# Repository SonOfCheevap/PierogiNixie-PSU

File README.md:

# PierogiNixie-PSU
A simple 12v to 150v-250v DC-DC Power supply for use with nixie tubes.

This is a modified version of an already existing PSU. Link to the original: https://www.electronics-lab.com/project/hv-nixie-dc-dc-switching-power-supply/

## New with V1.2
- Adjustable output AND hardwired resistor options available (150V-250V with variable resistor, 170V with set resistor)
- Cleaner routing
- Power planes
- Updated schematic to be more readable
- Included schematic as PDF
- Smaller Footprint

# Features
- 12v barrel jack input and wire input
- Adjustable output range of 150V to 250V (Only on V1 and V1.2)
- Wire output
- Mounting for M3.5x6 Screw

# Pictures
V1.2 AS OF 1/3/2025

### Front

### Back

### Render

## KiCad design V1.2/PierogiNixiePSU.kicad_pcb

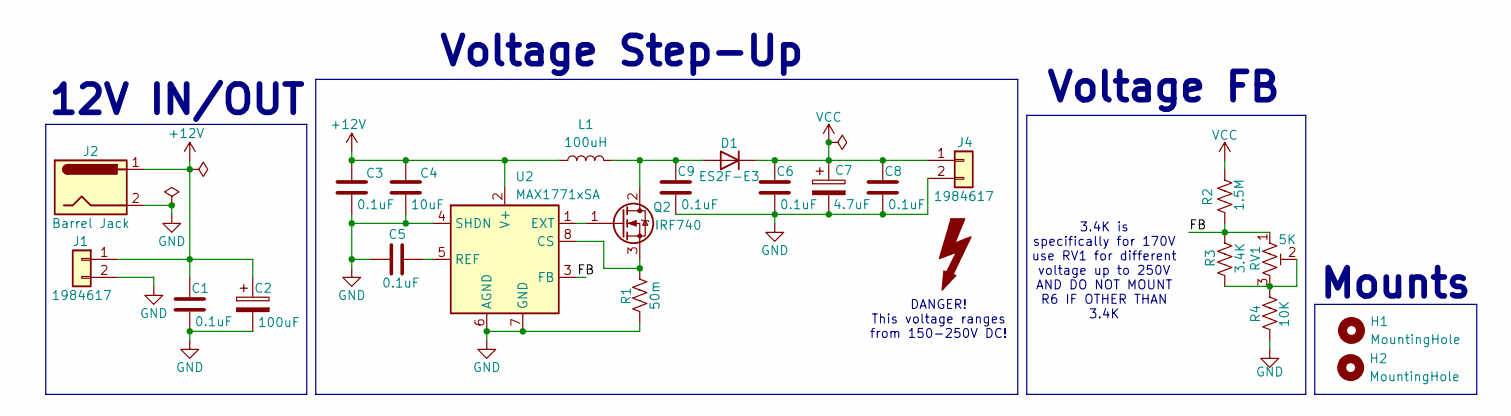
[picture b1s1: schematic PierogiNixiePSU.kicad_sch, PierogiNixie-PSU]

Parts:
C1, C3, C5, C6, C8, C9: 0.1uF; C_0805_2012Metric
C2: 100uF; CP_EIA-7343-30_AVX-N; Manufacturer_Part_Number TAJD107K020RNJ; Mouser Part Number 581-TAJD107K020R
C4: 10uF; C_0805_2012Metric
C7: 4.7uF; CP_Radial_D6.3mm_P2.50mm
D1: ES2F-E3; D_SMB_Handsoldering
H1, H2: MountingHole; MountingHole_3.5mm
J1, J4: 1984617; PhoenixContact_MCV_1,5_2-G-3.5_1x02_P3.50mm_Vertical
J2: Barrel Jack; BarrelJack_Kycon_KLDX-0202-xC_Horizontal
L1: 100uH; L_Vishay_IHLP-4040
Q2: IRF740; TO-263-2
R1: 50m; R_0805_2012Metric
R2: 1.5M; R_0805_2012Metric
R3: 3.4K; R_0805_2012Metric
R4: 10K; R_0805_2012Metric
RV1: 5K; Potentiometer_Bourns_3386P_Vertical
U2: MAX1771xSA; SO-8_3.9x4.9mm_P1.27mm

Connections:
+12V: C1.1, C2.1, C3.1, C4.1, J1.1, J2.1, L1.1, U2.2 (V+)
/FB: R2.1, R3.2, RV1.1, U2.3 (FB)
GND: C1.2, C2.2, C3.2, C4.2, C5.2, C6.2, C7.2, C8.2, C9.2, J1.2, J2.2, J4.2, R1.1, R4.2, U2.4 (SHDN), U2.6 (AGND), U2.7 (GND)
unnamed: C9.1, D1.2 (A), L1.2, Q2.2 (D)
unnamed: Q2.1 (G), U2.1 (EXT)
unnamed: Q2.3 (S), R1.2, U2.8 (CS)
unnamed: R3.1, R4.1, RV1.2, RV1.3
unnamed: C5.1, U2.5 (REF)
VCC: C6.1, C7.1, C8.1, D1.1 (K), J4.1, R2.2

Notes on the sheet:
Mounts
12V IN/OUT
Voltage FB
3.4K is specifically for 170V use RV1 for different voltage up to 250V AND DO NOT MOUNT R6 IF OTHER THAN 3.4K
Voltage Step-Up
DANGER! This voltage ranges from 150-250V DC!

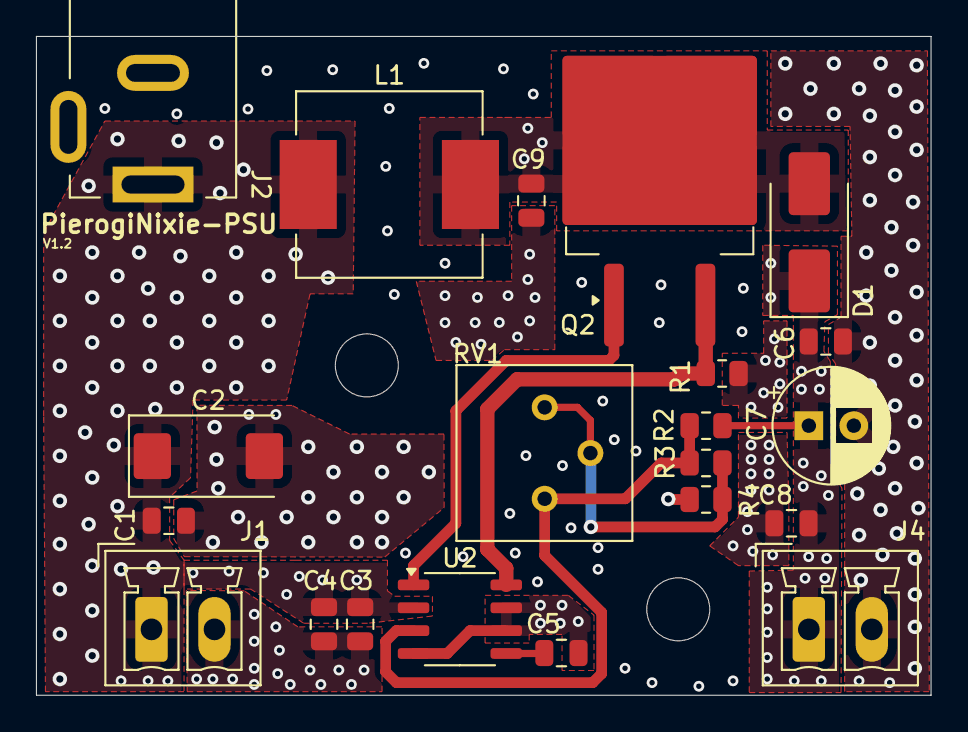
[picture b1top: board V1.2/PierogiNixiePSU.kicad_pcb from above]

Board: 4 copper layers, 49.7 x 36.6 mm, 23 parts (0 on the bottom side), 9 nets.

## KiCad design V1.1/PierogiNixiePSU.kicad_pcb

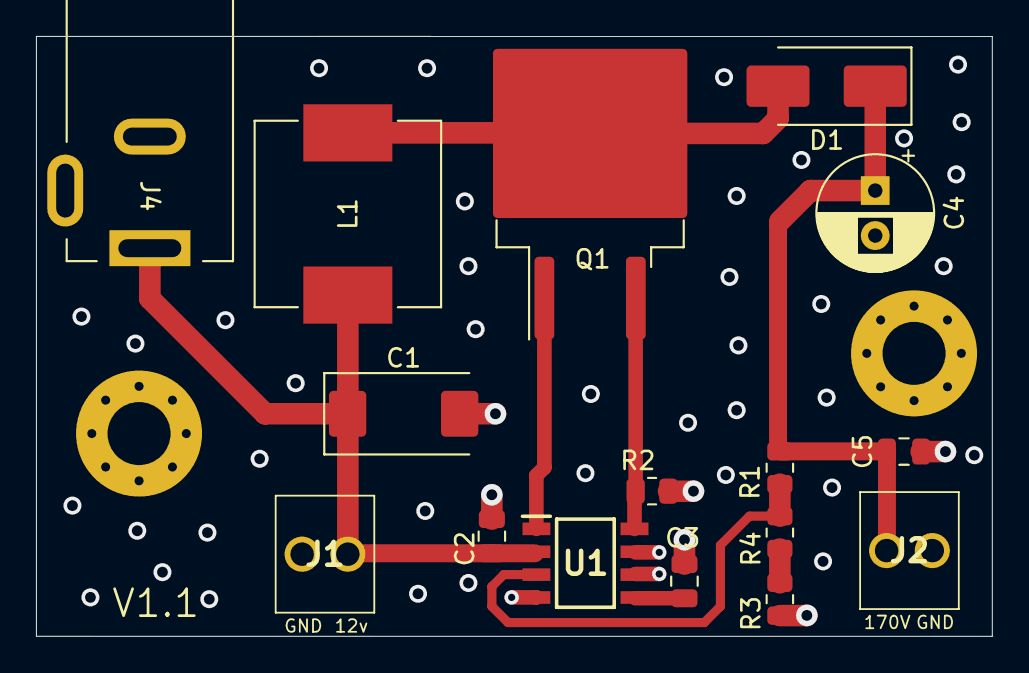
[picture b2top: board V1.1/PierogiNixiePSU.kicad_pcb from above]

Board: 4 copper layers, 53.1 x 33.3 mm, 18 parts (0 on the bottom side), 9 nets.

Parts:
C1: 100uF; CP_EIA-7343-30_AVX-N
C2, C3: 100nF; C_0805_2012Metric
C4: 4.7uF; CP_Radial_D6.3mm_P2.50mm
C5: .1uF; C_0805_2012Metric
D1: ES2F-E3; D_SMB_Handsoldering
H1, H2: MountingHole; MountingHole_3.5mm_Pad_Via
J1, J2: OSTVN02A150
J4: Barrel_Jack; BarrelJack_Kycon_KLDX-0202-xC_Horizontal
L1: 100uH; L_Vishay_IHLP-4040
Q1: IRF740STRLPBF; TO-263-2
R1: 1.5M; R_0805_2012Metric
R2: 50m; R_0805_2012Metric
R3: 10k; R_0805_2012Metric
R4: 3.4K; R_0805_2012Metric
U1: MAX1771CSAT; SOIC127P600X175-8N

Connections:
/CS: Q1.3 (S), R2.2, U1.8 (CS)
/EXT: Q1.1 (G), U1.1 (EXT)
/FB: R1.1, R4.2, U1.3 (FB)
GND: C1.2, C2.2, C3.2, C4.2, C5.2, J1.1, J2.2, J4.2, R2.1, R3.2, U1.4 (SHDN), U1.6 (AGND), U1.7 (GND)
unnamed: D1.2 (A), L1.2, Q1.2 (D)
unnamed: C4.1, C5.1, D1.1 (K), J2.1, R1.2
unnamed: R3.1, R4.1
unnamed: C3.1, U1.5 (REF)
unnamed: C1.1, C2.1, J1.2, J4.1, L1.1, U1.2 (V+)

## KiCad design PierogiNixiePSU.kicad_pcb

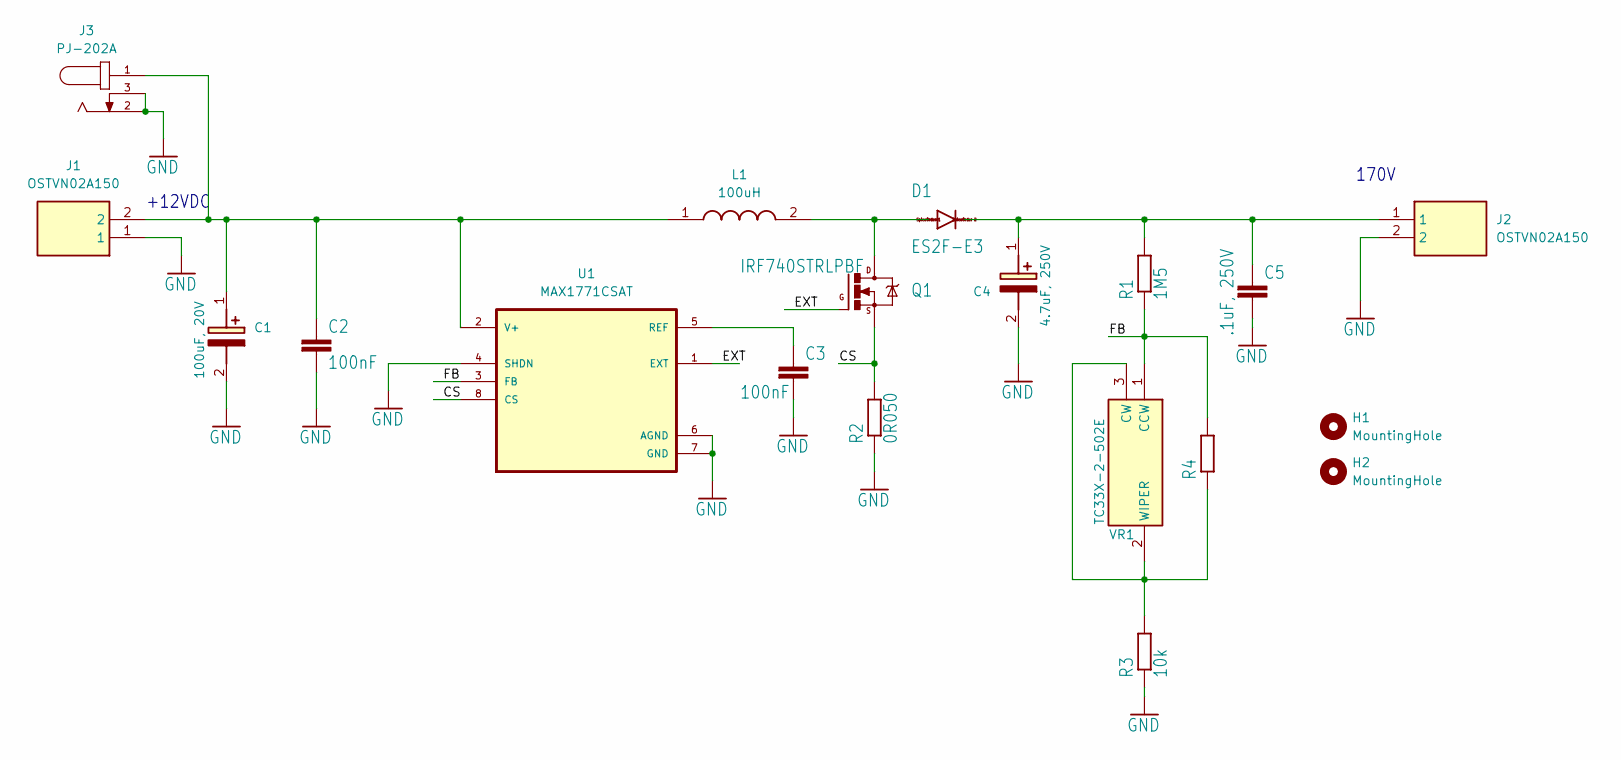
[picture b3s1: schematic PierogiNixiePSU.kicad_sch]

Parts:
C1: 100uF, 20V; CAPPM7344X310N; Manufacturer_Part_Number TAJD107K020RNJ; Mouser Part Number 581-TAJD107K020R
C2, C3: 100nF; C0805
C4: 4.7uF, 250V; CAPPRD250W50D655H1250; Manufacturer_Part_Number UVK2D0R1MED1TD
C5: .1uF, 250V; C0805
D1: ES2F-E3; SMB
H1, H2: MountingHole; MountingHole_3.5mm_Pad_Via
J1, J2: OSTVN02A150; Manufacturer_Part_Number OSTVN02A150
J3: PJ-202A; CUI_PJ-202A; PART_REV 1.02
L1: 100uH; INDPM108102X400N; Manufacturer_Part_Number IHLP4040DZER101M11; Mouser Part Number 70-IHLP4040DZER101M1
Q1: IRF740STRLPBF; TO-263_D2PAK
R1, R4: 1M5; R0805
R2: 0R050; R1206
R3: 10k; R0805
U1: MAX1771CSAT; SOIC127P600X175-8N
VR1: TC33X-2-502E; TC33X2503E; Manufacturer_Part_Number TC33X-2-502E; Mouser Part Number 652-TC33X-2-502E

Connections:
/CS: Q1.3 (S), R2.2, U1.8 (CS); also elsewhere on the board
/EXT: Q1.1 (G), U1.1 (EXT); also elsewhere on the board
/FB: R1.1, R4.2, U1.3 (FB), VR1.1 (CCW)
GND: C1.2 (-), C2.2, C3.2, C4.2 (-), C5.2, J1.1, J2.2, J3.2, J3.3, R2.1, R3.1, U1.4 (SHDN), U1.6 (AGND), U1.7 (GND)
unnamed: C1.1 (+), C2.1, J1.2, J3.1, L1.1, U1.2 (V+)
unnamed: C4.1 (+), C5.1, D1.C, J2.1, R1.2
unnamed 6: D1.A, L1.2, Q1.2 (D); also elsewhere on the board
unnamed: C3.1, U1.5 (REF)
unnamed: R3.2, R4.1, VR1.2 (WIPER), VR1.3 (CW)

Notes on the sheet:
+12VDC
170V

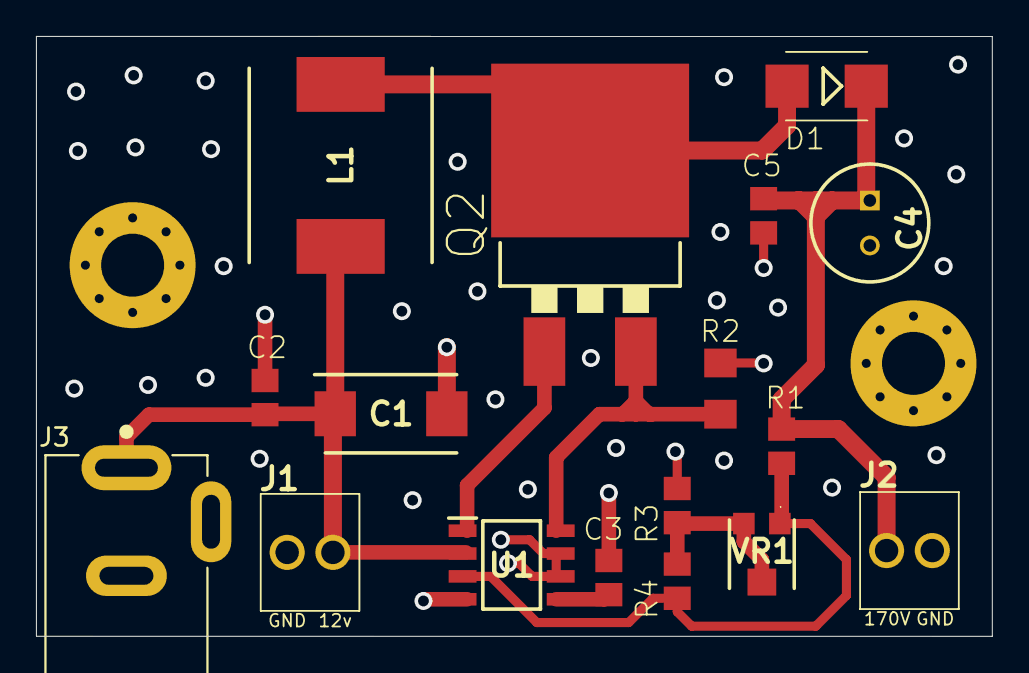
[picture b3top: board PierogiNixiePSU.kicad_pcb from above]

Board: 4 copper layers, 53.1 x 33.3 mm, 19 parts (0 on the bottom side), 9 nets.

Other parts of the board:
Q2: TO-263_D2PAK

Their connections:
/CS: Q2.3 (S); also elsewhere on the board
/EXT: Q2.1 (G); also elsewhere on the board
unnamed 6: Q2.2 (D); also elsewhere on the board

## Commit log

2023-07-07 Added DC barrel jack, updated BOM
2023-07-07 Added mounting hole
2023-07-08 Updated schematic and fixed thickness of GND traces
2023-07-23 Updated BOM
2023-12-12 Created v1.1 of the board
2023-12-12 dded Gerbers
2023-12-22 Updated gnd vias
2024-06-07 Create LICENSE
2025-01-04 Created V1.2 of PSU
2025-01-04 Updated reame
2025-01-04 Added render
